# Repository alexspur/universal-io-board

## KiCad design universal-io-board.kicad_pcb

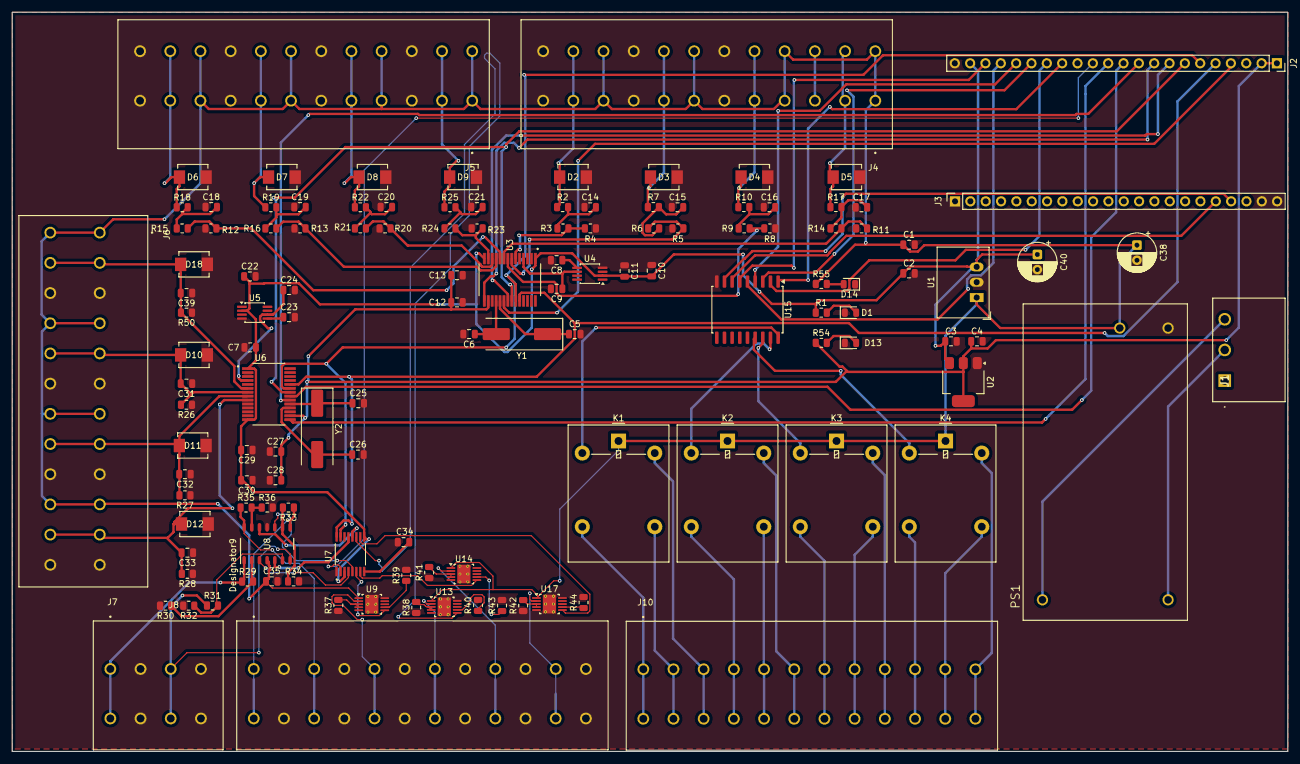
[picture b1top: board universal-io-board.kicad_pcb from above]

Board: 2 copper layers, 211.2 x 122.4 mm, 129 parts (0 on the bottom side), 109 nets.

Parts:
C1, C2, C3, C9, C11, C13, C24, C27, C29: 10uF; C_0805_2012Metric
C4: 22uF; C_0805_2012Metric
C5, C6, C25, C26: 18pF; C_0805_2012Metric
C7, C10, C12, C14, C15, C16, C17, C18, C19, C20, C21, C22, C28, C30, C31, C32, C33, C35, C39: 100nF; C_0805_2012Metric
C8, C23: 1uF; C_0805_2012Metric
C34: 2.2uF; C_0805_2012Metric
C38, C40: 100uF; CP_Radial_D6.3mm_P2.50mm
D1, D13, D14: LED; LED_0805_2012Metric
D2, D3, D4, D5, D6, D7, D8, D9, D10, D11, D12, D18: D_TVS; DO-214AASMB_J-BEND_LTF
J1: 1757255
J2, J3: Conn_01x22_Socket; PinSocket_1x22_P2.54mm_Vertical
J4, J5, J6, J8, J10: 1190374; PHOENIX_1190374
J7: 1190365; PHOENIX_1190365
K1, K2, K3, K4: G5LE-1; Relay_SPDT_Omron-G5LE-1
PS1: IRM-20-24; CONV_IRM-20-24
R1, R2, R7, R10, R17, R18, R19, R22, R25: 1k; R_0805_2012Metric
R3, R4, R5, R6, R8, R9, R11, R12, R13, R14, R15, R16, R20, R21, R23, R24, R29, R30, R31, R32, R33, R34, R35, R36, R55: 10k; R_0805_2012Metric
R26, R27, R28, R50: 249; R_0805_2012Metric
R37, R38, R41, R42: 100; R_0805_2012Metric
R39, R40, R43, R44: 20k; R_0805_2012Metric
R54: 330; R_0805_2012Metric
U1: R-78E5.0-1.0; Converter_DCDC_RECOM_R-78E-0.5_THT
U2: AMS1117-3.3; SOT-223-3_TabPin2
U3, U6: ADS1256IDBT; SOP65P780X200-28N
U4, U5: REF5050IDGK; MSOP-8_3x3mm_P0.65mm
U7: DAC8568ICPW; SOP65P640X120-16N
U8: OPA4192IDR; D0014A_N
U9, U13, U14, U17: XTR111AxDGQ; MSOP-10-1EP_3x3mm_P0.5mm_EP2.2x3.1mm_Mask1.83x1.89mm_Therma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
U15: ULN2803A; SOIC-18W_7.5x11.6mm_P1.27mm
Y1, Y2: Crystal; Crystal_SMD_HC49-SD

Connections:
+3.3V: C4.1, C12.2, C13.2, C27.2, C28.2, J2.1, J2.2, R54.1, U2.2 (VO), U3.16 (DVDD), U6.16 (DVDD)
+5V: C2.1, C3.1, C7.1, C10.2, C11.2, C22.1, C29.2, C30.2, C40.1, J2.21, R1.1, U1.3 (OUT), U2.3 (VI), U3.1 (AVDD), U3.14 (~SYNC,_~PDWN), U4.2 (Vin), U5.2 (Vin), U6.1 (AVDD), U6.14 (~SYNC,_~PDWN), U7.3 (AVDD), U7.9 (~CLR)
+24V: C1.1, C35.2, C38.1, J4.1_1, J4.1_2, J4.4_1, J4.4_2, J4.7_1, J4.7_2, J4.10_1, J4.10_2, J5.1_1, J5.1_2, J5.4_1, J5.4_2, J5.7_1, J5.7_2, J5.10_1, J5.10_2, J6.1_1, J6.1_2, J6.4_1, J6.4_2, J6.7_1, J6.7_2, J6.10_1, J6.10_2, K1.1, K2.1, K3.1, K4.1, PS1.4 (+V), R55.1, U1.1 (IN), U8.4 (V+), U9.1 (VSP), U13.1 (VSP), U14.1 (VSP), U17.1 (VSP)
/ADC2_CS: J2.10, U6.20 (~CS)
/ADC2_DRDY: J2.11, U6.21 (~DRDY)
/ADC2_RST: J2.12, U6.15 (~RESET)
/ADC_0-10V/A0: D2.1 (A1), J4.11_1, J4.11_2, R2.1
/ADC_0-10V/A1: D3.1 (A1), J4.8_1, J4.8_2, R7.1
/ADC_0-10V/A2: D4.1 (A1), J4.5_1, J4.5_2, R10.1
/ADC_0-10V/A3: D5.1 (A1), J4.2_1, J4.2_2, R17.1
/ADC_0-10V/A4: D6.1 (A1), J5.11_1, J5.11_2, R18.1
/ADC_0-10V/A5: D7.1 (A1), J5.8_1, J5.8_2, R19.1
/ADC_0-10V/A6: D8.1 (A1), J5.5_1, J5.5_2, R22.1
/ADC_0-10V/A7: D9.1 (A1), J5.2_1, J5.2_2, R25.1
/ADC_0-10V/AIN0: R3.2, R4.2, U3.6 (AIN0)
/ADC_0-10V/AIN1: R5.2, R6.2, U3.7 (AIN1)
/ADC_0-10V/AIN2: R8.2, R9.2, U3.8 (AIN2)
/ADC_0-10V/AIN3: R11.2, R14.2, U3.9 (AIN3)
/ADC_0-10V/AIN4: R12.2, R15.2, U3.10 (AIN4)
/ADC_0-10V/AIN5: R13.2, R16.2, U3.11 (AIN5)
/ADC_0-10V/AIN6: R20.2, R21.2, U3.12 (AIN6)
/ADC_0-10V/AIN7: R23.2, R24.2, U3.13 (AIN7)
/ADC_0-10V/VREFP: C9.1, U3.4 (VREFP), U4.6 (Vout)
/ADC_0-10V/XTAL1/CLKIN: C5.1, U3.19 (XTAL1/CLKIN), Y1.1
/ADC_0-10V/XTAL2: C6.1, U3.18 (XTAL2), Y1.2
/ADC_4-20mA/A0: C39.2, D18.1 (A1), J6.2_1, J6.2_2, R50.2, U6.6 (AIN0)
/ADC_4-20mA/A1: C31.2, D10.1 (A1), J6.5_1, J6.5_2, R26.2, U6.7 (AIN1)
/ADC_4-20mA/A2: C32.2, D11.1 (A1), J6.8_1, J6.8_2, R27.2, U6.8 (AIN2)
/ADC_4-20mA/A3: C33.2, D12.1 (A1), J6.11_1, J6.11_2, R28.2, U6.9 (AIN3)
/ADC_4-20mA/VREFP: C24.1, U5.6 (Vout), U6.4 (VREFP)
/ADC_4-20mA/XTAL1/CLKIN: C25.1, U6.19 (XTAL1/CLKIN), Y2.1
/ADC_4-20mA/XTAL2: C26.1, U6.18 (XTAL2), Y2.2
/ADC_CS: J2.4, U3.20 (~CS)
/ADC_DRDY: J2.8, U3.21 (~DRDY)
/ADC_RST: J2.9, U3.15 (~RESET)
/DAC Outputs (0-10V)/A0: J7.1_1, J7.1_2, R29.1, U8.1 (OUT)
/DAC Outputs (0-10V)/A1: J7.3_1, J7.3_2, R31.1, U8.7 (OUT)
/DAC Outputs (0-10V)/A2: J8.1_1, J8.1_2, R33.1, U8.8 (OUT)
/DAC Outputs (0-10V)/A3: J8.3_1, J8.3_2, R35.1, U8.14 (OUT)
/DAC Outputs (0-10V)/A4: J8.5_1, J8.5_2, U9.2 (IS)
/DAC Outputs (0-10V)/A5: J8.7_1, J8.7_2, U13.2 (IS)
/DAC Outputs (0-10V)/A6: J8.9_1, J8.9_2, U14.2 (IS)
/DAC Outputs (0-10V)/A7: J8.11_1, J8.11_2, U17.2 (IS)
/DAC Outputs (0-10V)/AO0: U7.4 (VOUTA), U8.3 (IN+)
/DAC Outputs (0-10V)/AO1: U7.13 (VOUTB), U8.5 (IN+)
/DAC Outputs (0-10V)/AO2: U7.5 (VOUTC), U8.10 (IN+)
/DAC Outputs (0-10V)/AO3: U7.12 (VOUTD), U8.12 (IN+)
/DAC Outputs (0-10V)/AO4: U7.6 (VOUTE), U9.6 (VIN)
/DAC Outputs (0-10V)/AO5: U7.11 (VOUTF), U13.6 (VIN)
/DAC Outputs (0-10V)/AO6: U7.7 (VOUTG), U14.6 (VIN)
/DAC Outputs (0-10V)/AO7: U7.10 (VOUTH), U17.6 (VIN)
/DAC_CS: J2.13, U7.2 (~SYNC)
/L: J1.3, PS1.1 (AC/L)
/N: J1.2, PS1.2 (AC/N)
/RELAY1: J2.15, U15.1 (I1)
/RELAY2: J2.16, U15.2 (I2)
/RELAY3: J2.17, U15.3 (I3)
/RELAY4: J2.18, U15.4 (I4)
/RELAY5: J2.19, U15.5 (I5)
/RELAY6: J2.20, U15.6 (I6)
/RELAY7: J3.18, U15.7 (I7)
/RELAY8: J3.19, U15.8 (I8)
/Relays/O1: K1.2, U15.18 (O1)
/Relays/O2: K2.2, U15.17 (O2)
/Relays/O3: K3.2, U15.16 (O3)
/Relays/O4: K4.2, U15.15 (O4)
/SPI_CLK: J2.5, U3.24 (SCLK), U6.24 (SCLK), U7.16 (SCLK)
/SPI_MISO: J2.7, U3.22 (DOUT), U6.22 (DOUT)
/SPI_MOSI: J2.6, U3.23 (DIN), U6.23 (DIN), U7.15 (DIN)
GND: C1.2, C2.2, C3.2, C4.2, C5.2, C6.2, C7.2, C8.2, C9.2, C10.1, C11.1, C12.1, C13.1, C14.1, C15.1, C16.1, C17.1, C18.1, C19.1, C20.1, C21.1, C22.2, C23.2, C24.2, C25.2, C26.2, C27.1, C28.1, C29.1, C30.1, C31.1, C32.1, C33.1, C34.2, C35.1, C38.2, C39.1, C40.2, D1.1 (K), D2.2 (A2), D3.2 (A2), D4.2 (A2), D5.2 (A2), D6.2 (A2), D7.2 (A2), D8.2 (A2), D9.2 (A2), D10.2 (A2), D11.2 (A2), D12.2 (A2), D13.1 (K), D14.1 (K), D18.2 (A2), J2.22, J3.1, J3.21, J3.22, J4.6_1, J4.6_2, J4.9_1, J4.9_2, J4.12_1, J4.12_2, J5.3_1, J5.3_2, J5.6_1, J5.6_2, J5.9_1, J5.9_2, J5.12_1, J5.12_2, J6.3_1, J6.3_2, J6.6_1, J6.6_2, J6.9_1, J6.9_2, J6.12_1, J6.12_2, J7.2_1, J7.2_2, J7.4_1, J7.4_2, J8.2_1, J8.2_2, J8.4_1, J8.4_2, J8.6_1, J8.6_2, J8.8_1, J8.8_2, J8.10_1, J8.10_2, J8.12_1, J8.12_2, PS1.3 (-V), R4.1, R5.1, R8.1, R11.1, R12.1, R13.1, R20.1, R23.1, R26.1, R27.1, R28.1, R30.2, R32.2, R34.2, R36.2, R37.1, R38.1, R39.2, R40.2, R41.1, R42.1, R43.2, R44.2, R50.1, U1.2 (GND), U2.1 (GND), U3.2 (AGND), U3.3 (VREFN), U3.5 (AINCOM), U3.17 (DGND), U4.4 (GND), U5.4 (GND), U6.2 (AGND), U6.3 (VREFN), U6.5 (AINCOM), U6.17 (DGND), U7.1 (~LDAC), U7.14 (GND), U8.11 (V-), U9.5 (REGF), U9.10 (GND), U9.11 (GND), U13.5 (REGF), U13.10 (GND), U13.11 (GND), U14.5 (REGF), U14.10 (GND), U14.11 (GND), U15.9 (GND), U17.5 (REGF), U17.10 (GND), U17.11 (GND)
unnamed: C14.2, R2.2, R3.1
unnamed: C15.2, R6.1, R7.2
unnamed: C16.2, R9.1, R10.2
unnamed: C17.2, R14.1, R17.2
unnamed: C18.2, R15.1, R18.2
unnamed: C19.2, R16.1, R19.2
unnamed: C20.2, R21.1, R22.2
unnamed: C21.2, R24.1, R25.2
unnamed: D1.2 (A), R1.2
unnamed: D13.2 (A), R54.2
unnamed: D14.2 (A), R55.2
unnamed: J4.3_1, J4.3_2
unnamed: J10.1_1, J10.1_2, K1.3
unnamed: J10.2_1, J10.2_2, K1.4
unnamed: J10.3_1, J10.3_2, K1.5
unnamed: J10.4_1, J10.4_2, K2.3
unnamed: J10.5_1, J10.5_2, K2.4
unnamed: J10.6_1, J10.6_2, K2.5
unnamed: J10.7_1, J10.7_2, K3.3
unnamed: J10.8_1, J10.8_2, K3.4
unnamed: J10.9_1, J10.9_2, K3.5
unnamed: J10.10_1, J10.10_2, K4.3
unnamed: J10.11_1, J10.11_2, K4.4
unnamed: J10.12_1, J10.12_2, K4.5
unnamed: C8.1, U4.5 (Trim/NR)
unnamed: C23.1, U5.5 (Trim/NR)
unnamed: C34.1, U7.8 (VREFIN/VREFOUT)
unnamed: R29.2, R30.1, U8.2 (IN-)
unnamed: R31.2, R32.1, U8.6 (IN-)
unnamed: R33.2, R34.1, U8.9 (IN-)
unnamed: R35.2, R36.1, U8.13 (IN-)
unnamed: R37.2, U9.3 (VG), U9.4 (REGS)
unnamed: R39.1, U9.7 (SET)
unnamed: R38.2, U13.3 (VG), U13.4 (REGS)
unnamed: R40.1, U13.7 (SET)
unnamed: R41.2, U14.3 (VG), U14.4 (REGS)
unnamed: R43.1, U14.7 (SET)
unnamed: R42.2, U17.3 (VG), U17.4 (REGS)
unnamed: R44.1, U17.7 (SET)

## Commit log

2026-03-28 Initial commit of universal-io-board
2026-03-28 Add project-specific libraries with relative paths
2026-03-28 Updated schematic and PCB
